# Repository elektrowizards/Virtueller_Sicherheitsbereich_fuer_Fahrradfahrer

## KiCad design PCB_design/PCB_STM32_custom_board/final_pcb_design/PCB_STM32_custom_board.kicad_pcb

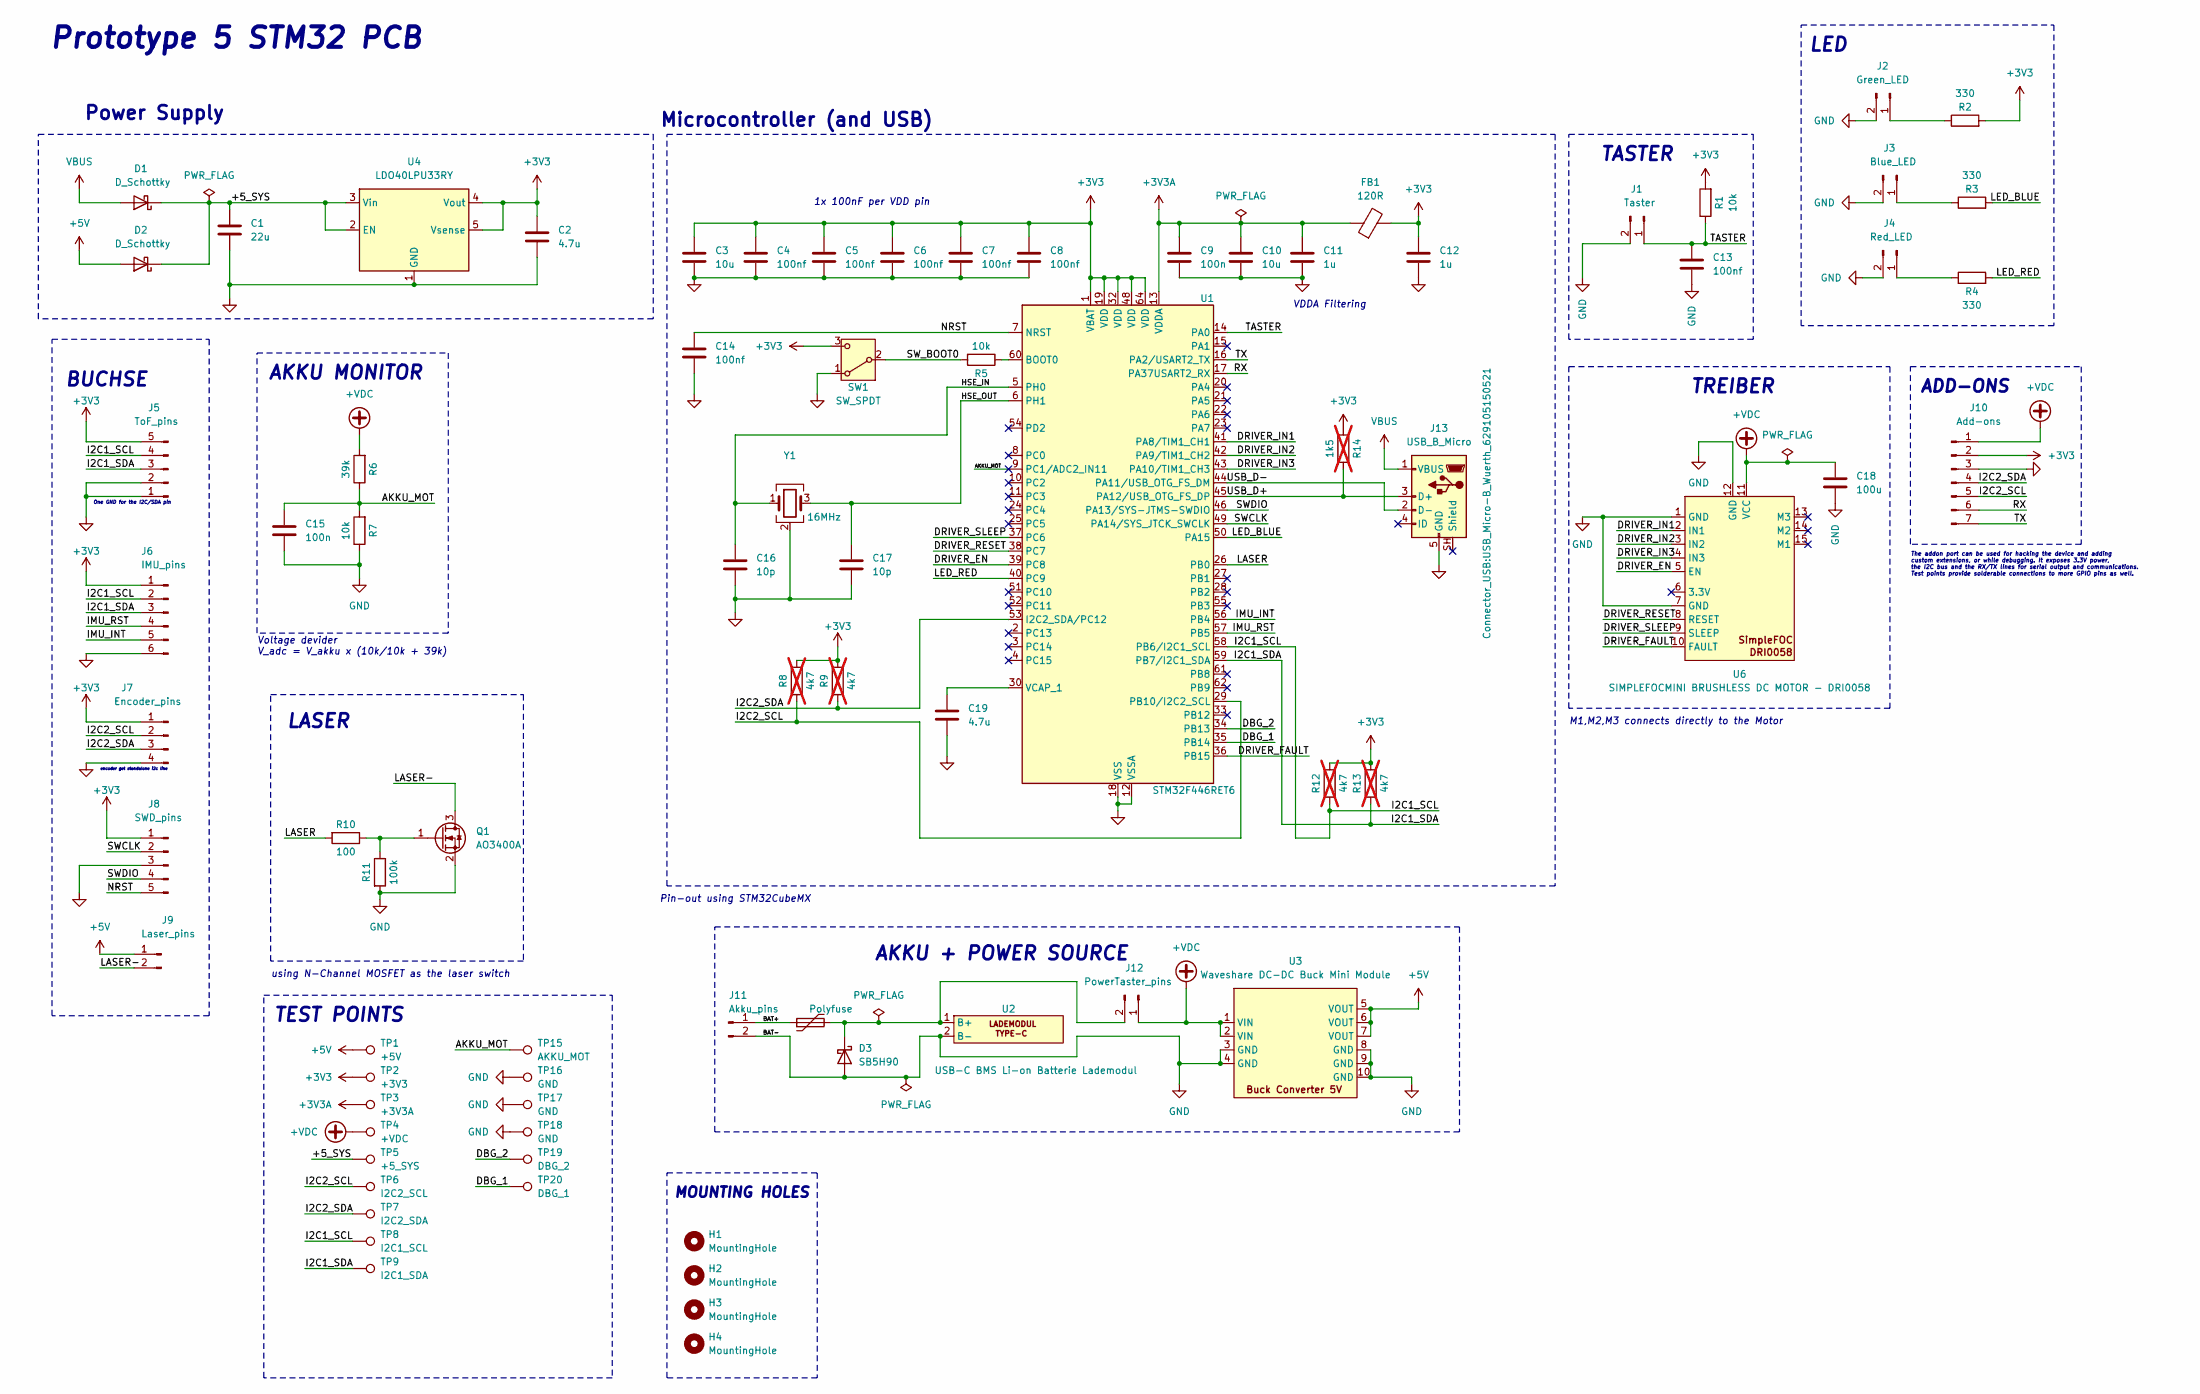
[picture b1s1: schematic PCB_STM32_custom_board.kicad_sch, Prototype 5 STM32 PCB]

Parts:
C1: 22u; C_0805_2012Metric
C2: 4.7u; C_0805_2012Metric
C3, C10: 10u; C_0603_1608Metric
C4, C5, C6, C7, C8, C13, C14: 100nf; C_0402_1005Metric
C9: 100n; C_0603_1608Metric
C11, C12: 1u; C_0402_1005Metric
C15: 100n; C_0805_2012Metric
C16, C17: 10p; C_0402_1005Metric
C18: 100u; CP_Radial_D6.3mm_P2.50mm
C19: 4.7u; C_0402_1005Metric
D1, D2: D_Schottky; D_SMA
D3: SB5H90; D_DO-201AD_P15.24mm_Horizontal
F1: Polyfuse; Fuse_Bourns_MF-RHT200
FB1: 120R; L_0603_1608Metric
H1, H2, H3, H4: MountingHole; MountingHole_2.2mm_M2_Pad
J1: Taster; JST_PH_B2B-PH-K_1x02_P2.00mm_Vertical
J2: Green_LED; JST_PH_B2B-PH-K_1x02_P2.00mm_Vertical
J3: Blue_LED; JST_PH_B2B-PH-K_1x02_P2.00mm_Vertical
J4: Red_LED; JST_PH_B2B-PH-K_1x02_P2.00mm_Vertical
J5: ToF_pins; JST_PH_B5B-PH-K_1x05_P2.00mm_Vertical
J6: IMU_pins; JST_PH_B6B-PH-K_1x06_P2.00mm_Vertical
J7: Encoder_pins; PinHeader_1x04_P2.54mm_Vertical
J8: SWD_pins; PinHeader_1x05_P2.54mm_Vertical
J9: Laser_pins; JST_PH_B2B-PH-K_1x02_P2.00mm_Vertical
J10: Add-ons; PinHeader_1x07_P2.54mm_Vertical
J11: Akku_pins; JST_PH_B2B-PH-K_1x02_P2.00mm_Vertical
J12: PowerTaster_pins; JST_PH_B2B-PH-K_1x02_P2.00mm_Vertical
J13: USB_B_Micro; USB_Micro-B_Wuerth_629105150521
Q1: AO3400A; SOT-23
R1, R5, R7: 10k; R_0402_1005Metric
R2, R3, R4: 330; R_0402_1005Metric
R6: 39k; R_0402_1005Metric
R8, R9, R12, R13: 4k7; R_Axial_DIN0207_L6.3mm_D2.5mm_P7.62mm_Horizontal; not fitted
R10: 100; R_0402_1005Metric
R11: 100k; R_0402_1005Metric
R14: 1k5; R_0402_1005Metric; not fitted
SW1: SW_SPDT; SW_SPDT_PCM12
TP1: +5V; TestPoint_Keystone_5000-5004_Miniature
TP2: +3V3; TestPoint_Keystone_5000-5004_Miniature
TP3: +3V3A; TestPoint_Keystone_5000-5004_Miniature
TP4: +VDC; TestPoint_Keystone_5000-5004_Miniature
TP5: +5_SYS; TestPoint_Keystone_5000-5004_Miniature
TP6: I2C2_SCL; TestPoint_Keystone_5000-5004_Miniature
TP7: I2C2_SDA; TestPoint_Keystone_5000-5004_Miniature
TP8: I2C1_SCL; TestPoint_Keystone_5000-5004_Miniature
TP9: I2C1_SDA; TestPoint_Keystone_5000-5004_Miniature
TP15: AKKU_MOT; TestPoint_Keystone_5000-5004_Miniature
TP16, TP17, TP18: GND; TestPoint_Bridge_Pitch2.0mm_Drill0.7mm
TP19: DBG_2; TestPoint_Keystone_5000-5004_Miniature
TP20: DBG_1; TestPoint_Keystone_5000-5004_Miniature
U1: STM32F446RET6; LQFP-64_10x10mm_P0.5mm
U2: USB-C BMS Li-on Batterie Lademodul; USB-C BMS Li-on Batterie Lademodul 3S 4.5V-15V 18W 3A
U3: Waveshare DC-DC Buck Mini Module; WAVESHARE_DC_DC_CONVERTER
U4: LDO40LPU33RY; DFN-6-1EP_3x3mm_P0.95mm_EP1.7x2.6mm
U6: SIMPLEFOCMINI BRUSHLESS DC MOTOR - DRI0058
Y1: 16MHz; Crystal_SMD_3225-4Pin_3.2x2.5mm

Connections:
+3V3: C2.1, C3.1, C4.1, C5.1, C6.1, C7.1, C8.1, C12.1, FB1.2, J5.5, J6.1, J7.1, J8.1, J10.2, R1.2, R2.2, R8.2, R9.2, R12.2, R13.2, R14.1, SW1.3 (C), TP2.1 (1_1), U1.1 (VBAT), U1.19 (VDD), U1.32 (VDD), U1.48 (VDD), U1.64 (VDD), U4.4 (Vout), U4.5 (Vsense)
+3V3A: C9.1, C10.1, C11.1, FB1.1, TP3.1 (1_1), U1.13 (VDDA)
+5V: D2.2 (A), J9.1, TP1.1 (1_1), U3.5 (VOUT), U3.6 (VOUT), U3.7 (VOUT)
+VDC: C18.1, J10.1, J12.1, R6.2, TP4.1 (1_1), U3.1 (VIN), U3.2 (VIN), U6.11 (VCC)
/+5_SYS: C1.1, D1.1 (K), D2.1 (K), TP5.1 (1_1), U4.2 (EN), U4.3 (Vin)
/AKKU_MOT: C15.1, R6.1, R7.2, TP15.1 (1_1), U1.9 (PC1/ADC2_IN11)
/BAT+: F1.1, J11.1
/DBG_1: TP20.1 (1_1), U1.35 (PB14)
/DBG_2: TP19.1 (1_1), U1.34 (PB13)
/DRIVER_EN: U1.39 (PC8), U6.5 (EN)
/DRIVER_FAULT: U1.36 (PB15), U6.10 (FAULT)
/DRIVER_IN1: U1.41 (PA8/TIM1_CH1), U6.2 (IN1)
/DRIVER_IN2: U1.42 (PA9/TIM1_CH2), U6.3 (IN2)
/DRIVER_IN3: U1.43 (PA10/TIM1_CH3), U6.4 (IN3)
/DRIVER_RESET: U1.38 (PC7), U6.8 (RESET)
/DRIVER_SLEEP: U1.37 (PC6), U6.9 (SLEEP)
/HSE_IN: C16.1, U1.5 (PH0), Y1.1
/HSE_OUT: C17.1, U1.6 (PH1), Y1.3
/I2C1_SCL: J5.4, J6.2, R12.1, TP8.1 (1_1), U1.58 (PB6/I2C1_SCL)
/I2C1_SDA: J5.3, J6.3, R13.1, TP9.1 (1_1), U1.59 (PB7/I2C1_SDA)
/I2C2_SCL: J7.2, J10.5, R8.1, TP6.1 (1_1), U1.29 (PB10/I2C2_SCL)
/I2C2_SDA: J7.3, J10.4, R9.1, TP7.1 (1_1), U1.53 (I2C2_SDA/PC12)
/IMU_INT: J6.5, U1.56 (PB4)
/IMU_RST: J6.4, U1.57 (PB5)
/LASER: R10.2, U1.26 (PB0)
/LASER-: J9.2, Q1.3 (D)
/LED_BLUE: R3.2, U1.50 (PA15)
/LED_RED: R4.2, U1.40 (PC9)
/NRST: C14.1, J8.5, U1.7 (NRST)
/RX: J10.6, U1.17 (PA37USART2_RX)
/SWCLK: J8.2, U1.49 (PA14/SYS_JTCK_SWCLK)
/SWDIO: J8.4, U1.46 (PA13/SYS-JTMS-SWDIO)
/SW_BOOT0: R5.2, SW1.2 (B)
/TASTER: C13.1, J1.1, R1.1, U1.14 (PA0)
/TX: J10.7, U1.16 (PA2/USART2_TX)
/USB_D+: J13.3 (D+), R14.2, U1.45 (PA12/USB_OTG_FS_DP)
/USB_D-: J13.2 (D-), U1.44 (PA11/USB_OTG_FS_DM)
GND: C1.2, C2.2, C3.2, C4.2, C5.2, C6.2, C7.2, C8.2, C9.2, C10.2, C11.2, C12.2, C13.2, C14.2, C15.2, C16.2, C17.2, C18.2, C19.2, D3.2 (A), J1.2, J2.2, J3.2, J4.2, J5.1, J5.2, J6.6, J7.4, J8.3, J10.3, J11.2, J13.5 (GND), Q1.2 (S), R7.1, R11.2, SW1.1 (A), TP16.1 (1_1), TP17.1 (1_1), TP18.1 (1_1), U1.12 (VSSA), U1.18 (VSS), U1.31 (VSS), U1.47 (VSS), U1.63 (VSS), U2.2 (B-), U3.3 (GND), U3.4 (GND), U3.8 (GND), U3.9 (GND), U3.10 (GND), U4.1 (GND), U4.7 (GND), U6.1 (GND), U6.7 (GND), U6.12 (GND), Y1.2 (G), Y1.4 (G)
unnamed: D3.1 (K), F1.2, J12.2, U2.1 (B+)
unnamed: J2.1, R2.1
unnamed: J3.1, R3.1
unnamed: J4.1, R4.1
unnamed: Q1.1 (G), R10.1, R11.1
unnamed: R5.1, U1.60 (BOOT0)
unnamed: C19.1, U1.30 (VCAP_1)
VBUS: D1.2 (A), J13.1 (VBUS)

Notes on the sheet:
VDDA Filtering
TREIBER
LASER
using N-Channel MOSFET as the laser switch
TASTER
LED
The addon port can be used for hacking the device and adding custom extensions, or while debugging. It exposes 3.3V power, the I2C bus and the RX/TX lines for serial output and communications. Test points provide solderable connections to more GPIO pins as well.
Power Supply
One GND for the I2C/SDA pin
AKKU MONITOR
Prototype 5 STM32 PCB
MOUNTING HOLES
Microcontroller (and USB)
Voltage devider V_adc = V_akku x (10k/10k + 39k)
1x 100nF per VDD pin
encoder get standalone i2c line
ADD-ONS
M1,M2,M3 connects directly to the Motor
AKKU + POWER SOURCE
TEST POINTS
BUCHSE
Pin-out using STM32CubeMX

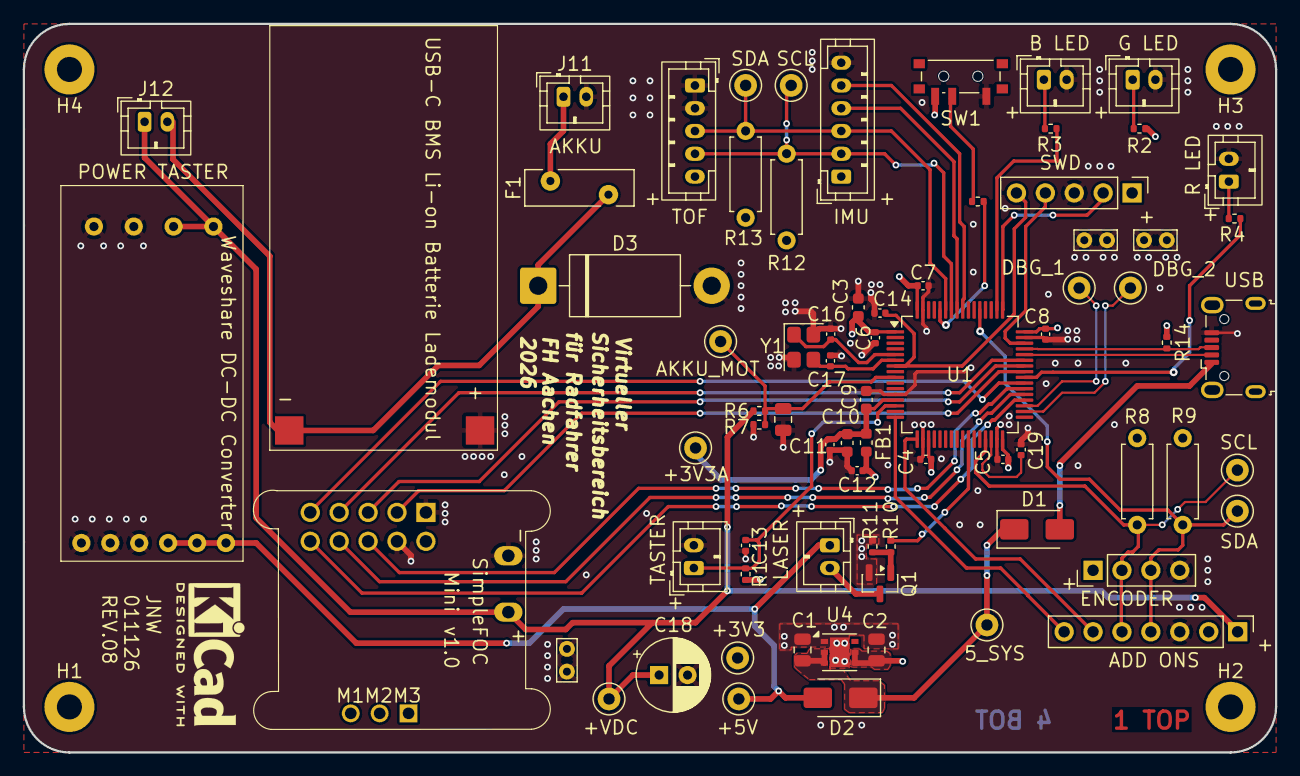
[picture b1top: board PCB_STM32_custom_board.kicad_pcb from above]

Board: 4 copper layers, 110.0 x 64.0 mm, 78 parts (0 on the bottom side), 46 nets.

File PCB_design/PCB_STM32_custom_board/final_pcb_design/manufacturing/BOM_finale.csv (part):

Bill Of Material ,,,,,,,,,
,,,,,,,,,
Item #,Designator,Footprint,Type,Qty,Designation,Manufacturer,MPN,Description,Link
1,C1,C_0805_2012Metric,SMD,1,22u,"Samsung Electro-Mechanics 
",CL21X226MAYNNWE,"Multilayer Ceramic Capacitors MLCC - SMD/SMT 22uF X6S +/-20% 25V 0805 
",https://www.mouser.de/en/ProductDetail/Samsung-Electro-Mecha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
2,C2,C_0805_2012Metric,SMD,1,4.7u,KEMET ,C0805C475K3RAC7210 , Multilayer Ceramic Capacitors MLCC - SMD/SMT 25V 4.7uF X7R 0805 10% ,https://www.mouser.de/en/ProductDetail/KEMET/C0805C475K3RAC7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
3,"C3, C10",C_0603_1608Metric,SMD,2,10u,KYOCERA AVX ,KGM15CR51E106KT ,Multilayer Ceramic Capacitors MLCC - SMD/SMT 25V 10uF X5R 0603 10 % ,https://www.mouser.de/en/ProductDetail/KYOCERA-AVX/KGM15CR51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
4,"C4, C5, C6, C7, C8, C13, C14",C_0402_1005Metric,SMD,7,100nf,"Samsung Electro-Mechanics 
",CL05B104KBD6PJC ,"Multilayer Ceramic Capacitors MLCC - SMD/SMT 0402/1005,100nF,X7R,50V,+/-10% ",https://www.mouser.de/en/ProductDetail/Samsung-Electro-Mecha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
5,C9,C_0603_1608Metric,SMD,1,100n,KEMET ,C0603C104K5RACTU ,Multilayer Ceramic Capacitors MLCC - SMD/SMT 50V 0.1uF X7R 0603 10%,https://www.mouser.de/en/ProductDetail/KEMET/C0603C104K5RACT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
6,"C11, C12",C_0402_1005Metric,SMD,2,1u,Murata Electronics ,"GRM155R61E105KE11D 

",Multilayer Ceramic Capacitors MLCC - SMD/SMT 1 uF 25 VDC 10% 0402 X5R ,https://www.mouser.de/en/ProductDetail/Murata-Electronics/GR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
7,C15,C_0805_2012Metric,SMD,1,100n,KEMET ,C0805R104J5RACTU ,Multilayer Ceramic Capacitors MLCC - SMD/SMT 50V 0.1uF X7R 0805 5% Flex Soft ,https://www.mouser.co.uk/en/ProductDetail/KEMET/C0805R104J5R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
8,"C16, C17",C_0402_1005Metric,SMD,2,10p,KEMET , C0402C100C5GACAUTO , Multilayer Ceramic Capacitors MLCC - SMD/SMT 50V 10pF C0G 0402 0.25pF AEC-Q200 ,https://www.mouser.com/ProductDetail/KEMET/C0402C100C5GACAUT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
9,C18,CP_Radial_D6.3mm_P2.50mm,thru-hole,1,100u,KEMET , ESC107M035AE3AA , Aluminium Electrolytic Capacitors - Radial Leaded 35V 100uF 105C 2k Hour Radial ,https://www.mouser.de/en/ProductDetail/KEMET/ESC107M035AE3AA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
10,C19,C_0402_1005Metric,SMD,1,4.7u,Samsung Electro-Mechanics,CL05A475MP7NRB8 , Multilayer Ceramic Capacitors MLCC - SMD/SMT 4.7uF+/-20% 10V X5R 0402 ,https://www.mouser.de/en/ProductDetail/Samsung-Electro-Mecha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
11,"D1, D2",D_SMA,SMD,2,D_Schottky,Diodes Incorporated ,B360AE-13 ,Schottky Diodes & Rectifiers Schottky Rectifier ,https://www.mouser.de/en/ProductDetail/Diodes-Incorporated/B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
12,D3,D_DO-201AD_P15.24mm_Horizontal,thru-hole,1,SB5H90,Vishay Semiconductors , SB5H90-E3/54 , Schottky Diodes & Rectifiers 90 Volt 5.0 Amp 200 Amp IFSM ,https://www.mouser.de/en/ProductDetail/Vishay-Semiconductors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
13,F1,Fuse_Bourns_MF-RHT200,thru-hole,1,Polyfuse,Bourns , MF-RHT200-0 , Resettable Fuses - PPTC PTC 2.0A 16V RADIAL LEADED HI-TEMP ,https://www.mouser.de/en/ProductDetail/Bourns/MF-RHT200-0?qs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
14,FB1,L_0603_1608Metric,SMD,1,120R,Eaton Electronics , MFBW1V1608-121-R , Ferrite Beads 120 OHM 1.0A ,https://www.mouser.de/en/ProductDetail/Eaton-Electronics/MFB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
15,J1,JST_PH_B2B-PH-K_1x02_P2.00mm_Vertical,thru-hole,1,Taster,JST Commercial ,B2B-PH-K-S(LF)(SN) ,Headers & Wire Housings PH SHROUDED HEADER ,https://www.mouser.de/en/ProductDetail/JST-Commercial/B2B-PH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
16,J2,JST_PH_B2B-PH-K_1x02_P2.00mm_Vertical,thru-hole,1,Green_LED,JST Commercial ,B2B-PH-K-S(LF)(SN) ,Headers & Wire Housings PH SHROUDED HEADER ,https://www.mouser.de/en/ProductDetail/JST-Commercial/B2B-PH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
17,J3,JST_PH_B2B-PH-K_1x02_P2.00mm_Vertical,thru-hole,1,Blue_LED,JST Commercial ,B2B-PH-K-S(LF)(SN) ,Headers & Wire Housings PH SHROUDED HEADER ,https://www.mouser.de/en/ProductDetail/JST-Commercial/B2B-PH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
18,J4,JST_PH_B2B-PH-K_1x02_P2.00mm_Vertical,thru-hole,1,Red_LED,JST Commercial ,B2B-PH-K-S(LF)(SN) ,Headers & Wire Housings PH SHROUDED HEADER ,https://www.mouser.de/en/ProductDetail/JST-Commercial/B2B-PH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
19,J5,JST_PH_B5B-PH-K_1x05_P2.00mm_Vertical,thru-hole,1,ToF_pins,JST Commercial ,B5B-PH-K-S(LF)(SN), Headers & Wire Housings PH HEADER (TOP) ,https://www.mouser.de/en/ProductDetail/JST-Commercial/B5B-PH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
20,J6,JST_PH_B6B-PH-K_1x06_P2.00mm_Vertical,thru-hole,1,IMU_pins,JST Commercial ,B6B-PH-K-S(LF)(SN), Headers & Wire Housings PA HEADER (TOP) ,https://www.mouser.de/en/ProductDetail/JST-Commercial/B6B-PH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
21,J7,PinHeader_1x04_P2.54mm_Vertical,DNS,1,Encoder_pins,,,,
22,J8,PinHeader_1x05_P2.54mm_Vertical,DNS,1,SWD_pins,,,,
23,J9,JST_PH_B2B-PH-K_1x02_P2.00mm_Vertical,thru-hole,1,Laser_pins,JST Commercial ,B2B-PH-K-S(LF)(SN) ,Headers & Wire Housings PH SHROUDED HEADER ,https://www.mouser.de/en/ProductDetail/JST-Commercial/B2B-PH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
24,J10,PinHeader_1x07_P2.54mm_Vertical,DNS,1,Add-ons,,,,
25,J11,JST_PH_B2B-PH-K_1x02_P2.00mm_Vertical,thru-hole,1,Akku_pins,JST Commercial ,B2B-PH-K-S(LF)(SN) ,Headers & Wire Housings PH SHROUDED HEADER ,https://www.mouser.de/en/ProductDetail/JST-Commercial/B2B-PH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
26,J12,JST_PH_B2B-PH-K_1x02_P2.00mm_Vertical,thru-hole,1,PowerTaster_pins,JST Commercial ,B2B-PH-K-S(LF)(SN) ,Headers & Wire Housings PH SHROUDED HEADER ,https://www.mouser.de/en/ProductDetail/JST-Commercial/B2B-PH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
27,J13,USB_Micro-B_Wuerth_629105150521,SMD,1,USB_B_Micro,Wurth Elektronik ,629105150521,USB Connectors WR-COM USB Micro SMT Type B Horiztl ,https://www.mouser.de/en/ProductDetail/Wurth-Elektronik/6291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
28,Q1,SOT-23,SMD,1,AO3400A,Alpha & Omega Semiconductor,AO3400A,The AO3400A combines advanced trench MOSFET technology with a low impedance package to provide ultra-low RDS(ON). This device is suitable for use as a load switch or in PWM applications.,https://www.reichelt.com/de/en/shop/product/mosfet_n-ch_30v_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
29,"R1, R5, R7",R_0402_1005Metric,SMD,3,10k,Panasonic, ERA2AEB103X,Metal film precision chip resistor,https://www.reichelt.com/de/en/shop/product/smd_chip_resisto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
30,"R2, R3, R4",R_0402_1005Metric,SMD,3,330,Kamaya, RMC1/16S-331JTH , Thick Film Resistors 0402 330R 5% ,https://www.mouser.de/en/ProductDetail/Kamaya/RMC1-16S-331JT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
31,R6,R_0402_1005Metric,SMD,1,39k,Kamaya, RMC10K3902FTH , Thick Film Resistors 39 KOhms 1% 0.5A AEC-Q200 ,https://www.mouser.de/en/ProductDetail/Kamaya/RMC10K3902FTH?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
32,"R8, R9, R12, R13",R_Axial_DIN0207_L6.3mm_D2.5mm_P7.62mm_Horizontal,DNS,4,4k7,,,,
33,R10,R_0402_1005Metric,SMD,1,100,Kamaya, RMC1/16S-101JTH , Thick Film Resistors 0402 100R 5% ,https://www.mouser.de/en/ProductDetail/Kamaya/RMC1-16S-101JT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
34,R11,R_0402_1005Metric,SMD,1,100k,Kamaya, RMC1/16S-104JTH , Thick Film Resistors 0402 100K 5% ,https://www.mouser.de/en/ProductDetail/Kamaya/RMC1-16S-104JT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
35,R14,R_0402_1005Metric,SMD,1,1k5,Kamaya ,RMC10K152FTH , Thick Film Resistors 1.5 kOhms 1% 0.5A AEC-Q200 ,https://www.mouser.de/en/ProductDetail/Kamaya/RMC10K152FTH?q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
36,SW1,SW_SPDT_PCM12,SMD,1,SW_SPDT,C&K ,PCM12SMTR , Slide Switches 0.3A SPDT ON-ON ,https://www.mouser.de/en/ProductDetail/CK/PCM12SMTR?qs=mfFuH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
37,TP1,TestPoint_Keystone_5000-5004_Miniature,DNS,1,+5V,,,,
38,TP2,TestPoint_Keystone_5000-5004_Miniature,DNS,1,+3V3,,,,
39,TP3,TestPoint_Keystone_5000-5004_Miniature,DNS,1,+3V3A,,,,
40,TP4,TestPoint_Keystone_5000-5004_Miniature,DNS,1,+VDC,,,,
41,TP5,TestPoint_Keystone_5000-5004_Miniature,DNS,1,+5_SYS,,,,
42,TP6,TestPoint_Keystone_5000-5004_Miniature,DNS,1,I2C2_SCL,,,,
43,TP7,TestPoint_Keystone_5000-5004_Miniature,DNS,1,I2C2_SDA,,,,
44,TP8,TestPoint_Keystone_5000-5004_Miniature,DNS,1,I2C1_SCL,,,,
45,TP9,TestPoint_Keystone_5000-5004_Miniature,DNS,1,I2C1_SDA,,,,
46,TP15,TestPoint_Keystone_5000-5004_Miniature,DNS,1,AKKU_MOT,,,,
47,"TP16, TP17, TP18",TestPoint_Bridge_Pitch2.0mm_Drill0.7mm,DNS,3,GND,,,,
48,TP19,TestPoint_Keystone_5000-5004_Miniature,DNS,1,DBG_2,,,,
49,TP20,TestPoint_Keystone_5000-5004_Miniature,DNS,1,DBG_1,,,,
50,U1,LQFP-64_10x10mm_P0.5mm,SMD,1,STM32F446RET6,STMicroelectronics , STM32F446RET6 ," ARM Microcontrollers - MCU High-performance foundation line, Arm Cortex-M4 core DSP & FPU, 512 Kbytes of Fl ",https://www.mouser.de/en/ProductDetail/STMicroelectronics/ST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
51,U2,USB-C BMS Li-on Batterie Lademodul 3S 4.5V-15V 18W 3A,DNS,1,USB-C BMS Li-on Batterie Lademodul,,,,
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
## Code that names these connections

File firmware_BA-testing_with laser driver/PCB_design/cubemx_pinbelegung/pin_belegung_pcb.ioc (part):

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Mcu.Name=STM32F446R(C-E)Tx
Mcu.Package=LQFP64
Mcu.UserName=STM32F446RETx
PA0-WKUP.GPIOParameters=GPIO_Label
PA0-WKUP.GPIO_Label=TASTER
PA0-WKUP.Signal=GPIO_Output
PA10.GPIOParameters=GPIO_Label
PA10.GPIO_Label=DRIVER_IN_3
PA10.Signal=S_TIM1_CH3
PA11.GPIOParameters=GPIO_Label
PA11.GPIO_Label=USB_D_-
PA11.Signal=USB_OTG_FS_DM
PA12.GPIOParameters=GPIO_Label
PA12.GPIO_Label=USB_D_+
PA12.Signal=USB_OTG_FS_DP
PA13.GPIOParameters=GPIO_Label
PA13.GPIO_Label=SWDIO
PA13.Signal=SYS_JTMS-SWDIO
PA14.GPIOParameters=GPIO_Label
PA14.GPIO_Label=SWCLK
PA14.Signal=SYS_JTCK-SWCLK
PA15.GPIOParameters=GPIO_Label
PA15.GPIO_Label=BLUE_LED
PA15.Signal=GPIO_Output
PA2.Mode=Asynchronous
PA2.Signal=USART2_TX
PA3.Mode=Asynchronous
PA3.Signal=USART2_RX
PA5.Mode=Full_Duplex_Master
PA5.Signal=SPI1_SCK
PA6.Mode=Full_Duplex_Master
PA6.Signal=SPI1_MISO
PA7.Mode=Full_Duplex_Master
PA7.Signal=SPI1_MOSI
PA8.GPIOParameters=GPIO_Label
PA8.GPIO_Label=DRIVER_IN_1
PA8.Signal=S_TIM1_CH1
PA9.GPIOParameters=GPIO_Label
PA9.GPIO_Label=DRIVER_IN_2
PA9.Signal=S_TIM1_CH2
PB0.GPIOParameters=GPIO_Label
PB0.GPIO_Label=LASER
PB0.Signal=GPIO_Output
PB10.Mode=I2C
PB10.Signal=I2C2_SCL
PB13.GPIOParameters=GPIO_Label
PB13.GPIO_Label=DBG_2
PB13.Signal=GPIO_Output
PB14.GPIOParameters=GPIO_Label
PB14.GPIO_Label=DBG_1
PB14.Signal=GPIO_Output
PB15.GPIOParameters=GPIO_Label
PB15.GPIO_Label=DRIVER_FAULT
PB15.Signal=GPIO_Input
PB4.GPIOParameters=GPIO_Label
PB4.GPIO_Label=IMU_INT
PB4.Signal=GPXTI4
PB5.GPIOParameters=GPIO_Label
PB5.GPIO_Label=IMU_RST
PB5.Signal=GPIO_Output
PB6.Mode=I2C
PB6.Signal=I2C1_SCL
PB7.Mode=I2C
PB7.Signal=I2C1_SDA
PC1.GPIOParameters=GPIO_Label
PC1.GPIO_Label=AKKU_MOT
PC1.Signal=ADCx_IN11
PC12.Mode=I2C
PC12.Signal=I2C2_SDA
PC6.GPIOParameters=GPIO_Label
PC6.GPIO_Label=DRIVER_SLEEP
PC6.Signal=GPIO_Output
PC7.GPIOParameters=GPIO_Label
PC7.GPIO_Label=DRIVER-RESET
PC7.Signal=GPIO_Output
PC8.GPIOParameters=GPIO_Label
PC8.GPIO_Label=DRIVER_EN
PC8.Signal=GPIO_Output
PC9.GPIOParameters=GPIO_Label
PC9.GPIO_Label=LED_RED
PC9.Signal=GPIO_Output
board=custom
